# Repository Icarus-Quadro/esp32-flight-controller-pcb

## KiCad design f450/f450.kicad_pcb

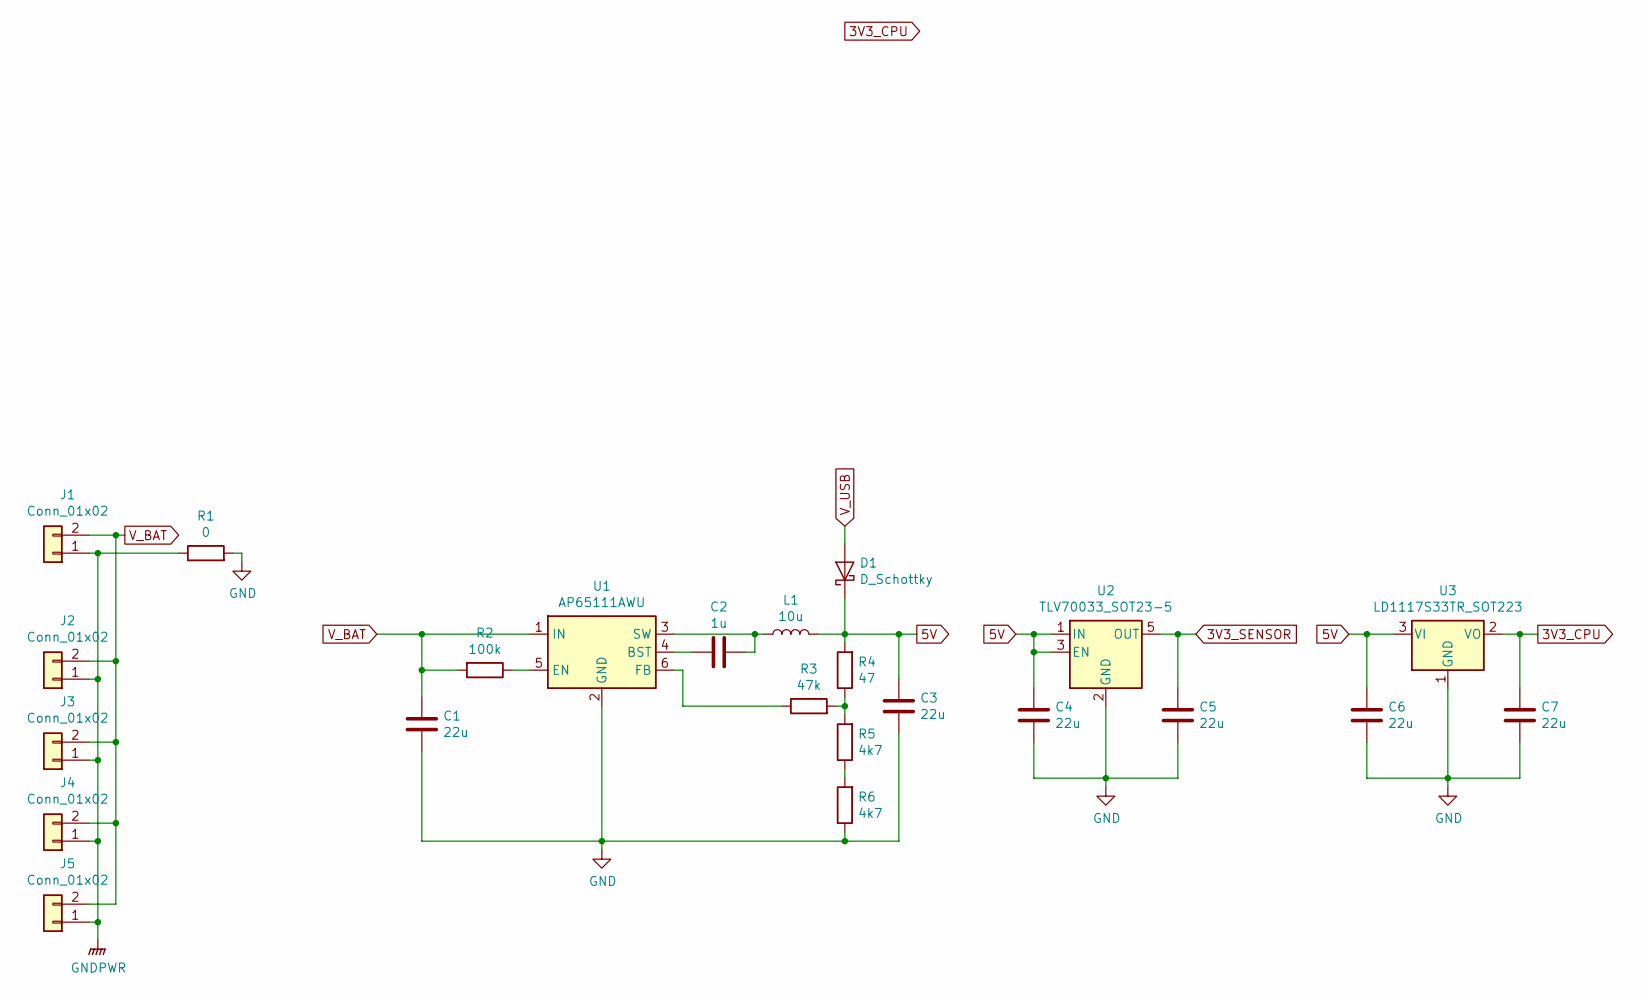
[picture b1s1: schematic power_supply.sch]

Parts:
C1, C3, C4, C5, C6, C7: 22u; C_0805_2012Metric_Pad1.15x1.40mm_HandSolder
C2: 1u; C_0805_2012Metric_Pad1.15x1.40mm_HandSolder
D1: D_Schottky; D_SMA_Handsoldering
J1: Conn_01x02; XT90PB-M
J2, J3, J4, J5: Conn_01x02; AMASS_XT30PW-F_1x02_P2.50mm_Horizontal
L1: 10u; L_Wuerth_MAPI-4020
R1: 0; R_0805_2012Metric_Pad1.15x1.40mm_HandSolder
R2: 100k; R_0805_2012Metric_Pad1.15x1.40mm_HandSolder
R3: 47k; R_0805_2012Metric_Pad1.15x1.40mm_HandSolder
R4: 47; R_0805_2012Metric_Pad1.15x1.40mm_HandSolder
R5, R6: 4k7; R_0805_2012Metric_Pad1.15x1.40mm_HandSolder
U1: AP65111AWU; TSOT-23-6
U2: TLV70033_SOT23-5; SOT-23-5
U3: LD1117S33TR_SOT223; SOT-223-3_TabPin2

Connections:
3V3_CPU: C7.1, U3.2 (VO); also elsewhere on the board
3V3_SENSOR: C5.1, U2.5 (OUT)
5V: C3.1, C4.1, C6.1, D1.1 (K), L1.2, R4.2, U2.1 (IN), U2.3 (EN), U3.3 (VI)
GND: C1.2, C3.2, C4.2, C5.2, C6.2, C7.2, R1.2, R6.1, U1.2 (GND), U2.2 (GND), U3.1 (GND); also elsewhere on the board
GNDPWR: J1.1, J2.1, J3.1, J4.1, J5.1, R1.1
unnamed: C2.1, U1.4 (BST)
unnamed: C2.2, L1.1, U1.3 (SW)
unnamed: R2.1, U1.5 (EN)
unnamed: R3.1, U1.6 (FB)
unnamed: R3.2, R4.1, R5.2
unnamed: R5.1, R6.2
V_BAT: C1.1, J1.2, J2.2, J3.2, J4.2, J5.2, R2.2, U1.1 (IN)

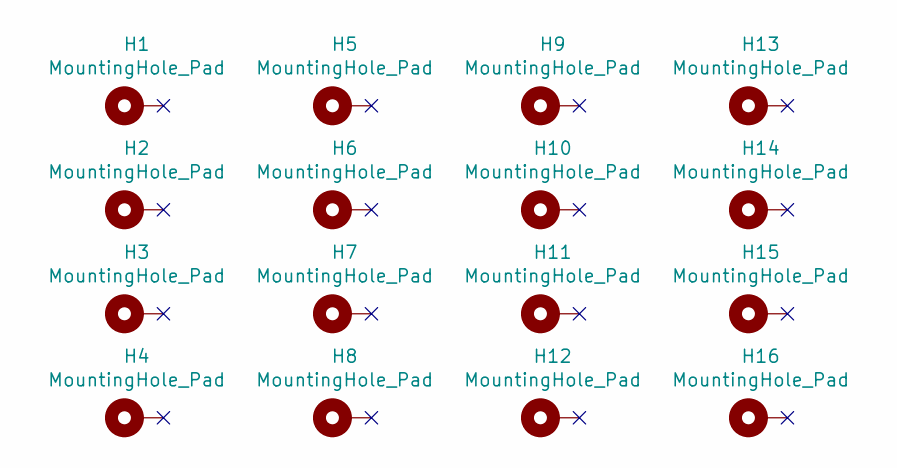
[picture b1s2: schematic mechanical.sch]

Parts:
H1, H2, H3, H4, H5, H6, H7, H8, H9, H10, H11, H12, H13, H14, H15, H16: MountingHole_Pad; MountingHole_3mm_Pad

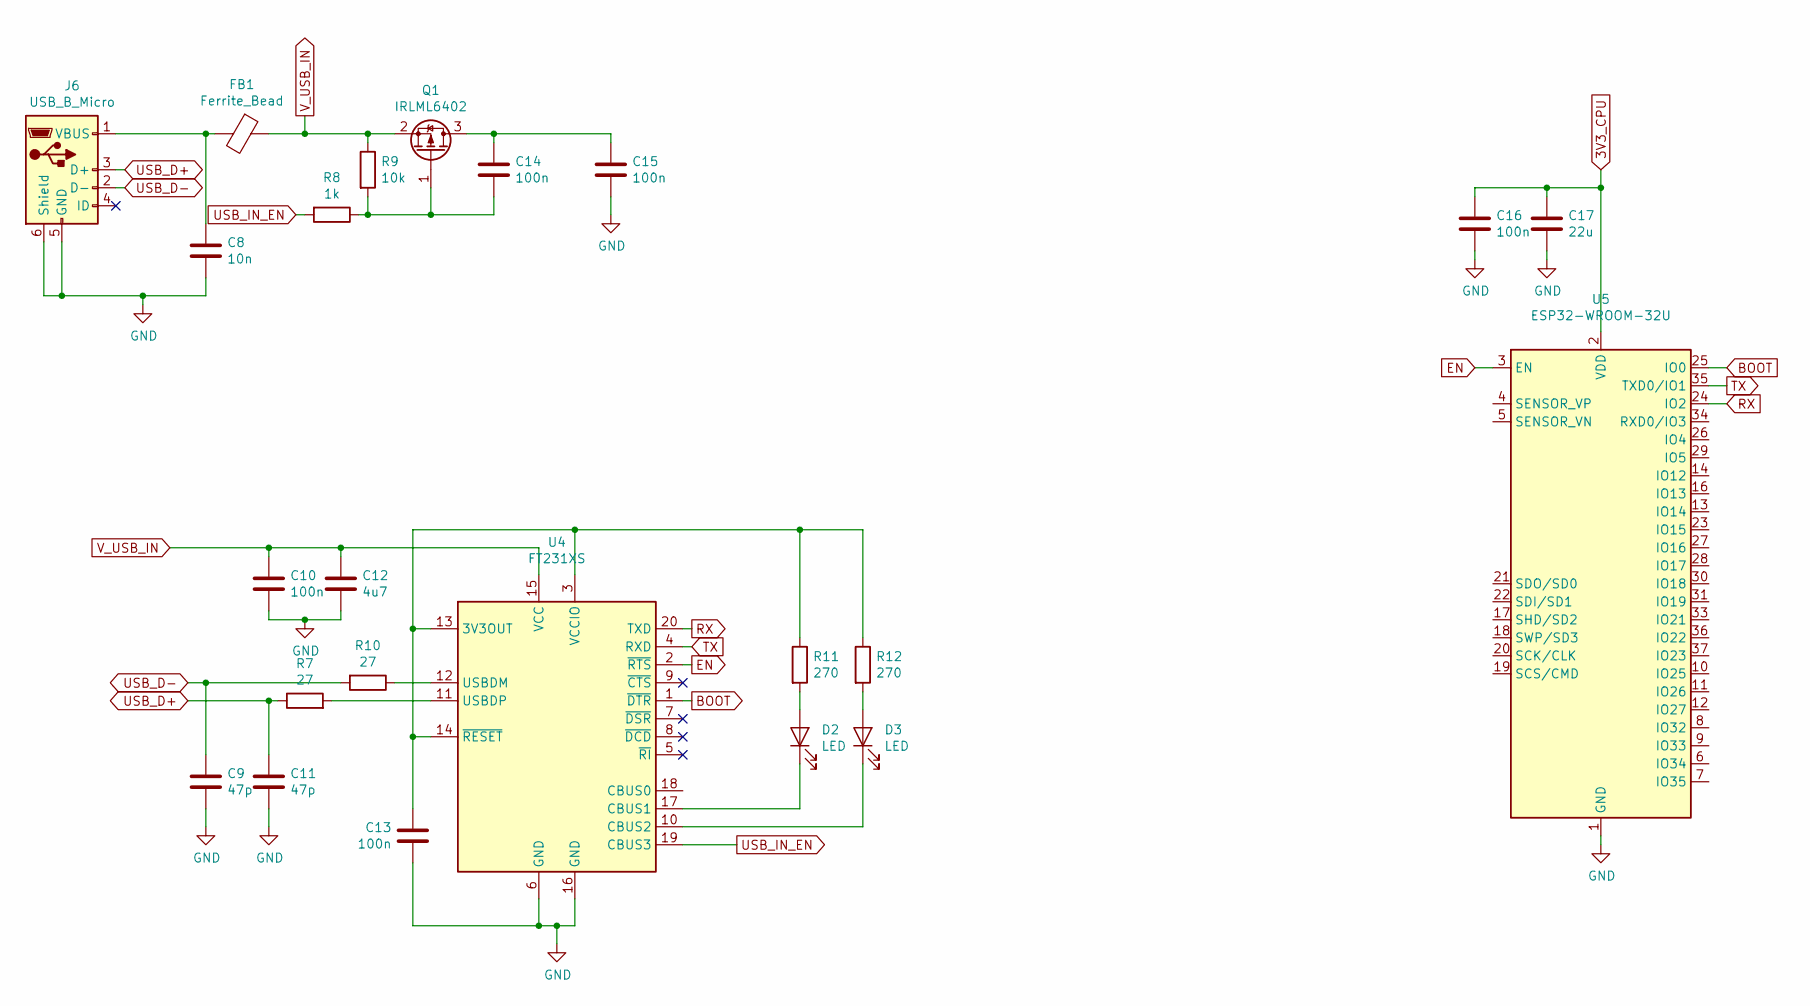
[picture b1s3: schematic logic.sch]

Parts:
C8: 10n; C_0805_2012Metric_Pad1.15x1.40mm_HandSolder
C9, C11: 47p; C_0805_2012Metric_Pad1.15x1.40mm_HandSolder
C10, C13, C14, C15, C16: 100n; C_0805_2012Metric_Pad1.15x1.40mm_HandSolder
C12: 4u7; C_0805_2012Metric_Pad1.15x1.40mm_HandSolder
C17: 22u; C_0805_2012Metric_Pad1.15x1.40mm_HandSolder
D2, D3: LED; LED_PLCC-2
FB1: Ferrite_Bead; L_2816_7142Metric_Pad3.20x4.45mm_HandSolder
J6: USB_B_Micro; USB_Micro-B_Amphenol_10103594-0001LF_Horizontal
Q1: IRLML6402; SOT-23
R7, R10: 27; R_0805_2012Metric_Pad1.15x1.40mm_HandSolder
R8: 1k; R_0805_2012Metric_Pad1.15x1.40mm_HandSolder
R9: 10k; R_0805_2012Metric_Pad1.15x1.40mm_HandSolder
R11, R12: 270; R_0805_2012Metric_Pad1.15x1.40mm_HandSolder
U4: FT231XS; SSOP-20_3.9x8.7mm_P0.635mm
U5: ESP32-WROOM-32U

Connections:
3V3_CPU: C16.1, C17.1, U5.2 (VDD); also elsewhere on the board
BOOT: U4.1 (~DTR), U5.25 (IO0)
EN: U4.2 (~RTS), U5.3 (EN)
GND: C8.2, C9.2, C10.2, C11.2, C12.2, C13.1, C15.2, C16.2, C17.2, J6.5 (GND), J6.6 (Shield), U4.6 (GND), U4.16 (GND), U5.1 (GND), U5.15 (GND), U5.38 (GND), U5.39 (GND); also elsewhere on the board
unnamed: C8.1, FB1.2, J6.1 (VBUS)
unnamed: C13.2, R11.1, R12.1, U4.3 (VCCIO), U4.13 (3V3OUT), U4.14 (~RESET)
unnamed: C14.1, C15.1, Q1.3 (D)
unnamed: C14.2, Q1.1 (G), R8.1, R9.2
unnamed: D2.1 (K), U4.17 (CBUS1)
unnamed: D2.2 (A), R11.2
unnamed: D3.1 (K), U4.10 (CBUS2)
unnamed: D3.2 (A), R12.2
unnamed: R7.2, U4.11 (USBDP)
unnamed: R10.1, U4.12 (USBDM)
RX: U4.20 (TXD), U5.24 (IO2)
TX: U4.4 (RXD), U5.35 (TXD0/IO1)
USB_D+: C11.1, J6.3 (D+), R7.1
USB_D-: C9.1, J6.2 (D-), R10.2
USB_IN_EN: R8.2, U4.19 (CBUS3)
V_USB_IN: C10.1, C12.1, FB1.1, Q1.2 (S), R9.1, U4.15 (VCC)

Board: 2 copper layers, 62 parts (0 on the bottom side), 30 nets, no tracks yet.

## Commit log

2020-03-02 WIP 5v voltage regulator. XT90 connector footprint.
2020-03-02 WIP power section.
2020-03-03 Added board CAD design. Schematic power section, USB-UART converter.
